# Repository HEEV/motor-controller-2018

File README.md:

# Cedarville University: Modular Motor Controller Project
### Senior Design project by Samuel Ellicott and Isaac Jones 2018-2019

You are in the hardware portion of the project, this contains the Kicad 
design files for the project and the schematics in PDF form. If you are 
looking for the software it is in the 
[motor controller 2018 sw](https://github.com/HEEV/motor-controller-2018-sw)
github repository. 

This project’s goal is to provide the Cedarville University Supermileage team with a high-efficiency electric motor controller for use in any category of vehicle. The controller should be simple enough to use that a competent freshman or sophomore engineer on the team could set it up. 

The controller is operated either by an analog throttle input or by the
CAN interface exposed by the controller. Hopefully this makes the controler
simple to use, but still capable of clever efficiency optimizations with
some wizardry.

The Cedarville supermileage team competes in the 
[Shell Eco-Marathon](https://www.shell.com/make-the-future/shell-ecomarathon.html)
so the design must fit within the contstraints of their rules (at the time of
this writting, 2019). This leads to the following constraints

* Maximum Nonminal Battery Voltage - 48V
* Peak Voltage - 60V

Therefore the controller was designed to fit these requirements and a new
driver stage would need to be designed if these limits were exceeded.

```
Even though I have graduated I am still more than willing to answer questions about this project :-) 

-Sam Ellicott
```

## Project Organization
Overall, the project is organized into two gitub repositories. 
This one, devoted to the motor controller hardware
([motor controller 2018](https://github.com/HEEV/motor-controller-2018))
and the other one ([motor controller 2018 sw](https://github.com/HEEV/motor-controller-2018-sw)) devoted to the motor controller
software.

The actual hardware of the project is split into three PCBs 
(and three corresponding Kcad projects)

The hardware repository is split between three [Kicad](http://kicad-pcb.org/)
projects.

* [motor-controller-hw](motor-controller-hw/): 
  This somewhat poorly named project contains the 
  files for the controller portion of the project (micocontroller, 
  FOC algorithm chip, inputs, etc)
* [MotorControllerPowerBoardRev2](MotorControllerPowerBoardRev2/MotorControllerPowerBoard):
  This contains (somewhat obviously) the Kicad project for the 
  power conversion part of the motor controller (FET driver chips, giant
  honking power MOSFETS, current sensing chips, etc). The power stage has 
  four NFET half bridges and three hall-effect current sensing chips.
  The board can be configured to power a 3-phase motor or a brushed motor.
  Optionally for the brushed motor the half-bridges can be parralled to 
  double the drive current capability. 
* [voltage-regulator-module](voltage-regulator-module/): 
  We were unable to find a commertially available 60V-to-5v DC-DC converter 
  for the controller portion of the project that did not have significant
  lead time, so we rolled our own to fit a similar footprint to some
  DC-DC converters from Pololu. This is just a little daughter PCB that
  is soldered to the controller PCB.  

The schematic files and PDF's of the PCB layout can be found in the 
[pdf](pdf) directory.

## Software versions
For this project we used either Kicad version 5.0.1 or 5.0.2 
(I cannot really remember), but it will probably work with any version
of Kicad > 5.0.0

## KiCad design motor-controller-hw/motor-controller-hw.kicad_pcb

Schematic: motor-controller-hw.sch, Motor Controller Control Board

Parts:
C101, C104, C105: 4u7; C_0805_HandSoldering; Digi-key# 732-7628-1-ND
C102: 100n; C_0805_HandSoldering; Digi-key# 1276-2444-1-ND
C103: 33u; CP_Radial_D8.0mm_P3.50mm; Digi-key# P10340-ND
D101: 15V Zener; D_SOD-123F; Digi-key# BZT52HC15WF-7DICT-ND‎
D102: D_USB; D_SOD-123F; Digi-key# MBR1020VLCT-ND‎
D103: Vin; LED_0603_HandSoldering; Digi-key# 732-12015-1-ND
D104: 5V; LED_0603_HandSoldering; Digi-key# 732-12015-1-ND
D105: 3.3V; LED_0603_HandSoldering; Digi-key# 732-12015-1-ND
F101, F102, F103, F105: 50mA PTC; Fuse_0603_1608Metric_Pad1.05x0.95mm_HandSolder; Digi-key# 507-1816-1-ND
F104: 120mA PTC; Fuse_0603_1608Metric_Pad1.05x0.95mm_HandSolder; Digi-key# 507-1819-1-ND
J101: CAN; Molex-duraClick-4conn; Digi-key# WM7171CT-ND
J102: Throttle; Molex-duraClick-4conn; Digi-key# WM7171CT-ND
J103: Motor T; Molex-duraClick-2conn; Digi-key# WM7169CT-ND
J104: Tran T; Molex-duraClick-2conn; Digi-key# WM7169CT-ND
J105: USB_B_Micro; USB_Micro-B; Digi-key# 609-4618-1-ND
J106: Extra IO; Molex-UltraFit-14p-vert; Digi-key# WM11743-ND‎
J107: Hall Sensors; MICRO_JST_6; Digi-key# 455-1708-ND
J108: CAN_DBG; PinHeader_1x02_P2.54mm_Vertical; Digi-key# S1212EC-02-ND
J109: ABN Encoder; PinHeader_1x05_P2.54mm_Vertical; Digi-key# S1212EC-05-ND
J110: SPI_DBG; PinHeader_1x04_P2.54mm_Vertical; Digi-key# S1212EC-04-ND
J111: Trinamic-Bridge; PinSocket_2x22_P2.54mm_Vertical; Digi-key# S7125-ND
JP101: 5v JP; PinHeader_1x02_P2.54mm_Vertical; Digi-key# S1212EC-02-ND
Q101: Q_PMOS_GDS; TO-252-3_TabPin2; Digi-key# 785-1102-1-ND
R101, R102, R103: 10K; R_0805_HandSoldering; Digi-key# A129761CT-ND
R104: 1K; R_0805_HandSoldering; Digi-key# A129749CT-ND
R105: 330R; R_0805_HandSoldering; Digi-key# 311-330CRCT-ND
TP101: Batt_TP; PinHeader_1x02_P2.54mm_Vertical; Digi-key# N/A
TP102: 5v_TP; PinHeader_1x02_P2.54mm_Vertical; Digi-key# N/A
TP103: 3v3_TP; PinHeader_1x02_P2.54mm_Vertical; Digi-key# N/A
TP104, TP105: GND_TP; PinHeader_1x01_P2.54mm_Vertical; Digi-key# N/A
U101: AP7361C-33; SOT-223; Digi-key# AP7361C-33E-13DICT-ND
U102: D36V6F5; D36V6Fx

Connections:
+3V3: C104.1, C105.1, F103.2, R101.1, R105.2, TP103.2, U101.3; also elsewhere on the board
+5V: C101.1, C102.1, D102.1, F101.1, F102.2, F104.1, F105.2, J109.5, J111.42, R104.2, TP102.2, U101.1, U102.1; also elsewhere on the board
+BATT: C103.1, D101.1, Q101.3, R103.2, TP101.2, U102.3; also elsewhere on the board
/ADC_I_A: J111.15; also elsewhere on the board
/ADC_I_B: J111.14; also elsewhere on the board
/A_Out1: J106.10; also elsewhere on the board
/A_Out2: J106.11; also elsewhere on the board
/A_in1: J106.3; also elsewhere on the board
/A_in2: J106.4; also elsewhere on the board
/Batt_Current: J111.16; also elsewhere on the board
/Brake: J111.36; also elsewhere on the board
/CAN_H: J101.3; also elsewhere on the board
/CAN_L: J101.2; also elsewhere on the board
/D_Out1: J106.12; also elsewhere on the board
/D_Out2: J106.13; also elsewhere on the board
/D_in1: J106.5; also elsewhere on the board
/D_in2: J106.6; also elsewhere on the board
/D_in3: J106.7; also elsewhere on the board
/D_in4: J106.14; also elsewhere on the board
/ENC_A_in: J109.4; also elsewhere on the board
/ENC_B_in: J109.3; also elsewhere on the board
/ENC_N_in: J109.2; also elsewhere on the board
/En_Out: J111.40; also elsewhere on the board
/HallA_in: J107.3; also elsewhere on the board
/HallB_in: J107.4; also elsewhere on the board
/HallC_in: J107.5; also elsewhere on the board
/IO Protection/CAN_Rx: J108.1; also elsewhere on the board
/IO Protection/CAN_Tx: J108.2; also elsewhere on the board
/MotorTemp: J103.2, J107.2, R101.2; also elsewhere on the board
/PWM_AH: J111.18; also elsewhere on the board
/PWM_AL: J111.17; also elsewhere on the board
/PWM_BH: J111.20; also elsewhere on the board
/PWM_BL: J111.19; also elsewhere on the board
/PWM_CH: J111.22; also elsewhere on the board
/PWM_CL: J111.21; also elsewhere on the board
/PWM_DH: J111.26; also elsewhere on the board
/PWM_DL: J111.23; also elsewhere on the board
/PWM_Idle_H: J111.34; also elsewhere on the board
/PWM_Idle_L: J111.35; also elsewhere on the board
/SPI_MISO: J111.28; also elsewhere on the board
/SPI_MOSI: J111.32; also elsewhere on the board
/SPI_SCK: J111.27; also elsewhere on the board
/SPI_SS: J111.24; also elsewhere on the board
/TMC4671/SPI_MISO: J110.3; also elsewhere on the board
/TMC4671/SPI_MOSI: J110.4; also elsewhere on the board
/TMC4671/SPI_SCK: J110.2; also elsewhere on the board
/TMC4671/~SPI_CS: J110.1; also elsewhere on the board
/Throttle: J102.2; also elsewhere on the board
/TransistorTemp: J104.2; also elsewhere on the board
/USB_D+: J105.3; also elsewhere on the board
/USB_D-: J105.2; also elsewhere on the board
/V_USB: D102.2, J105.1
/Vin: J111.1, Q101.2
GNDD: C101.2, C102.2, C103.2, C104.2, C105.2, D103.1, D104.1, D105.1, J101.1, J102.1, J103.1, J104.1, J105.5, J105.6, J106.1, J106.2, J107.6, J109.1, J111.2, J111.3, J111.43, J111.44, R102.2, TP101.1, TP102.1, TP103.1, TP104.1, TP105.1, U101.2, U102.2; also elsewhere on the board
unnamed: D101.2, Q101.1, R102.1
unnamed: D103.2, R103.1
unnamed: D104.2, R104.1
unnamed: D105.2, R105.1
unnamed: F101.2, J102.3, J102.4
unnamed: F102.1, J106.8
unnamed: F103.1, J106.9
unnamed: F104.2, JP101.2
unnamed: F105.1, J107.1
unnamed: J101.4, JP101.1

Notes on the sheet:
3.3V linear voltage regulator for the low voltage electronics. The selected regulator can supply 1A of output current, which is more than what the 5V switching regulator can supply. The 4.7uF output capacitor should have a fairly low ESR.
5V switching regulator, up to 50V input, maximum 600mA output current. The regulator is short circuit protected. A P-Channel MOSFET is used as an ideal diode with a 18v zener diode to protect the MOSFET gate. The 10K resistor limits the zener diode current to 3mA at 48V input. A Schotty diode is us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
Power supply test points
PWM_Ax, PWM_Bx, and PWM_Cx correspond to the A, B, and C phases of a three phase motor. The PWM_Dx lines are for a "extra" fourth phase. Note that the A, B, and C lines may be labeled U, V, and W elsewhere which are their european designation.
Digital Comm
Analog IO
Encoders
Power Status LEDs

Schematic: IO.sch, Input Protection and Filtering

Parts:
C201, C204, C205, C206, C207, C208, C209, C210, C211: 100n; C_0805_HandSoldering; Digi-key# 1276-2444-1-ND
C202, C212, C213: 1u; C_0805_HandSoldering; Digi-key# 732-7672-1-ND
C203: 150n; C_0805_HandSoldering; Digi-key# 732-7674-1-ND
C214: 4u7; C_0805_HandSoldering; Digi-key# 732-7628-1-ND
C215, C216, C217, C218, C219, C220: 100p; C_0805_HandSoldering; Digi-key# 1276-1014-1-ND
JP201: CAN Term; PinHeader_1x02_P2.54mm_Vertical
R201, R202, R203, R204, R205: 2K; R_0805_HandSoldering
R206: 3K9; R_0805_HandSoldering
R207, R208, R209, R213, R214, R215: 100R; R_0805_HandSoldering
R210, R211, R212, R217, R218, R219: 4K7; R_0805_HandSoldering
R216: 120R; R_0805_HandSoldering
R220: 10K; R_0805_HandSoldering
U201, U202, U203: MCP6004; SOIC-14_3.9x8.7mm_P1.27mm; Digi-key# MCP6004-I/SL-ND‎
U204, U205: 74HC7014; SOIC-14_3.9x8.7mm_P1.27mm; Digi-key# 1727-6342-1-ND
U206: mcp2562; SOIC-8_3.9x4.9mm_P1.27mm; Digi-key# 568-11881-1-ND

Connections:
+3V3: C208.1, C209.1, C210.1, C211.1, C212.1, C213.1, C214.1, U202.4, U203.4, U204.14, U205.14, U206.5; also elsewhere on the board
+5V: C201.1, C202.1, R210.1, R211.1, R212.1, R217.1, R218.1, R219.1, U201.4, U206.3; also elsewhere on the board
/A_Out1: U201.6, U201.7; also elsewhere on the board
/A_Out2: U201.1, U201.2; also elsewhere on the board
/A_in1: U203.3; also elsewhere on the board
/A_in2: U203.10; also elsewhere on the board
/CAN_H: R216.1, U206.7; also elsewhere on the board
/CAN_L: JP201.1, U206.6; also elsewhere on the board
/D_Out1: U204.10; also elsewhere on the board
/D_Out2: U204.12; also elsewhere on the board
/D_in1: U204.1; also elsewhere on the board
/D_in2: U204.3; also elsewhere on the board
/D_in3: U204.5; also elsewhere on the board
/D_in4: U204.9; also elsewhere on the board
/ENC_A: U205.8; also elsewhere on the board
/ENC_A_in: R213.2; also elsewhere on the board
/ENC_B: U205.10; also elsewhere on the board
/ENC_B_in: R214.2; also elsewhere on the board
/ENC_N: U205.12; also elsewhere on the board
/ENC_N_in: R215.2; also elsewhere on the board
/HallA: U205.2; also elsewhere on the board
/HallA_in: R207.2; also elsewhere on the board
/HallB: U205.4; also elsewhere on the board
/HallB_in: R208.2; also elsewhere on the board
/HallC: U205.6; also elsewhere on the board
/HallC_in: R209.2; also elsewhere on the board
/IO Protection/A_In1: U203.6, U203.7; also elsewhere on the board
/IO Protection/A_In2: U203.13, U203.14; also elsewhere on the board
/IO Protection/A_Out1: U201.5; also elsewhere on the board
/IO Protection/A_Out2: U201.3; also elsewhere on the board
/IO Protection/CAN_Rx: U206.4; also elsewhere on the board
/IO Protection/CAN_Tx: U206.1; also elsewhere on the board
/IO Protection/D_In1: U204.2; also elsewhere on the board
/IO Protection/D_In2: U204.4; also elsewhere on the board
/IO Protection/D_In3: U204.6; also elsewhere on the board
/IO Protection/D_In4: U204.8; also elsewhere on the board
/IO Protection/D_Out1: U204.11; also elsewhere on the board
/IO Protection/D_Out2: U204.13; also elsewhere on the board
/IO Protection/MotorTemp: U202.6, U202.7; also elsewhere on the board
/IO Protection/Throttle: U201.13, U201.14; also elsewhere on the board
/IO Protection/TransistorTemp: U202.13, U202.14; also elsewhere on the board
/MotorTemp: U202.3; also elsewhere on the board
/Throttle: U201.10; also elsewhere on the board
/TransistorTemp: U202.10; also elsewhere on the board
GNDD: C201.2, C202.2, C203.2, C204.2, C205.2, C206.2, C207.2, C208.2, C209.2, C210.2, C211.2, C212.2, C213.2, C214.2, C215.2, C216.2, C217.2, C218.2, C219.2, C220.2, R206.1, R220.1, U201.11, U202.11, U203.11, U204.7, U205.7, U206.2; also elsewhere on the board
unnamed: C203.1, R201.1, R206.2, U201.12
unnamed: C204.1, R202.1, U202.5
unnamed: C205.1, R203.1, U202.12
unnamed: C206.1, R204.1, U203.5
unnamed: C207.1, R205.1, U203.12
unnamed: C215.1, R207.1, R210.2, U205.1
unnamed: C216.1, R208.1, R211.2, U205.3
unnamed: C217.1, R209.1, R212.2, U205.5
unnamed: C218.1, R213.1, R217.2, U205.9
unnamed: C219.1, R214.1, R218.2, U205.11
unnamed: C220.1, R215.1, R219.2, U205.13
unnamed: JP201.2, R216.2
unnamed: R201.2, U201.8, U201.9
unnamed: R202.2, U202.1, U202.2
unnamed: R203.2, U202.8, U202.9
unnamed: R204.2, U203.1, U203.2
unnamed: R205.2, U203.8, U203.9
unnamed: R220.2, U206.8

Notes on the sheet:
Rail to rail op-amp necessary for the filter section to work correctly. Throttle and output buffers run off 5v supply, all others on 3.3v to prevent ADC damage.
Buffer input stage
Attenuator and Filter Selected for 750Hz cutoff 1.5Khz Sampling rate
Buffer output stage
Output Buffers
Input Buffers
Hall Input Filtering
Power and Bypass Capacitors
MCP2562 may be replaced with a TJF1051T/3. Pin 5 on the TJF1051T/3 is a silent mode enable pin which is active high, so the circuit still works.
CAN Tranciever PHY
This sheet contains input/output proteciton and conditioning circuitry. Note that the stm32 USB lines pass through this sheet without modification.
ABN Encoder Input Filtering
Schmitt trigger inputs for taking out noise

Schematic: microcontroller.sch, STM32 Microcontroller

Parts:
C301, C302, C303, C304, C305, C311: 100n; C_0805_HandSoldering; Digi-key# 1276-2444-1-ND
C306: 4u7; C_0805_HandSoldering; Digi-key# 732-7628-1-ND
C307: 1u; C_0805_HandSoldering; Digi-key# 732-7672-1-ND
C308: 10n; C_0805_HandSoldering; Digi-key# 732-12169-1-ND
C309, C310: 27pf; C_0805_HandSoldering; Digi-key# 1276-2622-1-ND
D301: CAN_Status; LED_0603_1608Metric_Pad1.05x0.95mm_HandSolder; Digi-key# 732-12013-1-ND
D302: Heartbeat; LED_0603_1608Metric_Pad1.05x0.95mm_HandSolder; Digi-key# 732-12015-1-ND
D303: User_LED; LED_0603_1608Metric_Pad1.05x0.95mm_HandSolder; Digi-key# 732-12017-1-ND
J301: SWD; PinHeader_1x06_P2.54mm_Vertical; Digi-key# S1212EC-06-ND
J302: User USART; PinHeader_1x03_P2.54mm_Vertical; Digi-key# S1212EC-03-ND
R301: 10K; R_0805_HandSoldering; Digi-key# A129761CT-ND
R302, R306, R307: 330R; R_0805_HandSoldering; Digi-key# 311-330CRCT-ND
R303: 4K7; R_0805_HandSoldering; Digi-key# 311-4.70KCRCT-ND
R304, R305: 100R; R_0805_HandSoldering; Digi-key# 311-100CRCT-ND
R308: 1K5; R_0805_2012Metric
SW301: Reset; SW_SPST_FSMSM; Digi-key# 450-1758-1-ND
SW302: Boot; SW_SPST_FSMSM; Digi-key# 450-1758-1-ND
SW303: User_SW; SW_SPST_FSMSM; Digi-key# 450-1758-1-ND
U301: STM32F303RETx; LQFP-64_10x10mm_P0.5mm; Digi-key# 497-15163-ND
Y301: 8Mhz; Crystal_SMD_HC49-SD_HandSoldering; Digi-key# 535-10212-1-ND‎

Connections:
+3V3: C301.1, C302.1, C304.1, C305.1, C306.1, C307.1, C308.1, J301.1, R303.1, R308.1, SW302.2, U301.1 (VBAT), U301.13 (VDDA), U301.19 (VDD), U301.32 (VDD), U301.48 (VDD), U301.64 (VDD); also elsewhere on the board
/IO Protection/A_In1: U301.23 (PA7); also elsewhere on the board
/IO Protection/A_In2: U301.24 (PC4); also elsewhere on the board
/IO Protection/A_Out1: U301.20 (PA4); also elsewhere on the board
/IO Protection/A_Out2: U301.21 (PA5); also elsewhere on the board
/IO Protection/CAN_Rx: U301.61 (PB8); also elsewhere on the board
/IO Protection/CAN_Tx: U301.62 (PB9); also elsewhere on the board
/IO Protection/D_In1: U301.37 (PC6); also elsewhere on the board
/IO Protection/D_In2: U301.38 (PC7); also elsewhere on the board
/IO Protection/D_In3: U301.39 (PC8); also elsewhere on the board
/IO Protection/D_In4: U301.40 (PC9); also elsewhere on the board
/IO Protection/D_Out1: U301.41 (PA8); also elsewhere on the board
/IO Protection/D_Out2: U301.42 (PA9); also elsewhere on the board
/IO Protection/MotorTemp: U301.14 (PA0); also elsewhere on the board
/IO Protection/Throttle: U301.22 (PA6); also elsewhere on the board
/IO Protection/TransistorTemp: U301.15 (PA1); also elsewhere on the board
/SPI_MISO: U301.53 (PC12); also elsewhere on the board
/SPI_MOSI: U301.52 (PC11); also elsewhere on the board
/SPI_SCK: U301.51 (PC10); also elsewhere on the board
/SPI_SS: U301.50 (PA15); also elsewhere on the board
/STM32/Boot: R301.1, SW302.1, U301.60 (BOOT0)
/STM32/CAN_Status: R305.2, U301.26 (PB0)
/STM32/Heartbeat: R306.2, U301.27 (PB1)
/STM32/JTCK: J301.2, U301.49 (PA14)
/STM32/JTMS: J301.4, U301.46 (PA13)
/STM32/OSC+: C309.1, U301.5 (PF0), Y301.2
/STM32/OSC-: R302.1, U301.6 (PF1)
/STM32/Reset: C303.1, J301.5, SW301.2, U301.7 (NRST)
/STM32/SWO: J301.6, U301.55 (PB3)
/STM32/USART_Rx: J302.3, U301.17 (PA3)
/STM32/USART_Tx: J302.2, U301.16 (PA2)
/STM32/User_LED: R307.2, U301.28 (PB2)
/STM32/User_SW: C311.1, R303.2, SW303.2, U301.2 (PC13)
/TMC4671/En_In: U301.29 (PB10); also elsewhere on the board
/TMC4671/SPI_MISO: U301.35 (PB14); also elsewhere on the board
/TMC4671/SPI_MOSI: U301.36 (PB15); also elsewhere on the board
/TMC4671/SPI_SCK: U301.34 (PB13); also elsewhere on the board
/TMC4671/Status: U301.30 (PB11); also elsewhere on the board
/TMC4671/~SPI_CS: U301.33 (PB12); also elsewhere on the board
/USB_D+: R308.2, U301.45 (PA12); also elsewhere on the board
/USB_D-: U301.44 (PA11); also elsewhere on the board
GNDD: C301.2, C302.2, C303.2, C304.2, C305.2, C306.2, C307.2, C308.2, C309.2, C310.2, D301.1, D302.1, D303.1, J301.3, J302.1, R301.2, R304.2, SW301.1, SW303.1, U301.12 (VSSA), U301.18 (VSS), U301.31 (VSS), U301.47 (VSS), U301.63 (VSS); also elsewhere on the board
unnamed: C310.1, R302.2, Y301.1
unnamed: C311.2, R304.1
unnamed: D301.2, R305.1
unnamed: D302.2, R306.1
unnamed: D303.2, R307.1

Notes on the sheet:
Bypass Capacitors, one for each Vdd pin, and a 4.7uf cap for good measure. Also two bypass capacitors (1uf and 10nf) for the ADC and DAC.
Crystal Oscilator with 18pf load capacitor rating. Assumed stray capacitance of 5pf. See: https://www.allaboutcircuits.com/technical-articles/ choosing-the-right-oscillator-for-your-microcontroller/
Reset and Boot switches for programming the microcontroller with the USB bootloader. SWD connector for in system debugging of the microcontroller.
User Inputs and Outputs
1.5 KOhm pull up: enable USB programming

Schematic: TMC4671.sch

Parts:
C401, C402, C403, C404, C405, C406, C407, C408, C409, C412, C413, C414, C415: 100n; C_0805_HandSoldering; Digi-key# 1276-2444-1-ND
C410: 470n; C_0805_HandSoldering; Digi-key# 732-7670-1-ND
C411, C416: 4u7; C_0805_HandSoldering; Digi-key# 732-7628-1-ND
C417, C418, C419, C420: 10n; C_0805_HandSoldering; Digi-key# 732-12169-1-ND
J401: Trinamic_TRMI; DF20F-10DP-1V(56); Digi-key# H10726CT-ND
J402: TMC4671 USART; PinHeader_1x03_P2.54mm_Vertical; Digi-key# S1212EC-03-ND
R401, R402, R403, R404, R405, R408, R409: 10K; R_0805_HandSoldering; Digi-key# A129761CT-ND
R406, R407: 100R; R_0805_HandSoldering; Digi-key# 311-100CRCT-ND
R410: 110K; R_0805_HandSoldering; Digi-key# 311-110KCRCT-ND
TP401: B_Ref; Pin_Header_Straight_1x01_Pitch2.54mm; Digi-key# N/A
TP402: A_Ref; Pin_Header_Straight_1x01_Pitch2.54mm; Digi-key# N/A
TP403, TP404, TP405, TP406, TP407, TP408, TP409, TP410, TP411, TP412, TP413, TP414, TP415, TP416, TP417, TP418: TestPoint; TestPoint_Pad_D1.0mm; Digi-key# N/A
TP419: A_I_TP; PinHeader_1x02_P2.54mm_Vertical; Digi-key# N/A
TP420: B_I_TP; PinHeader_1x02_P2.54mm_Vertical; Digi-key# N/A
TP421: Batt_V_TP; PinHeader_1x02_P2.54mm_Vertical; Digi-key# N/A
TP422: Batt_I_TP; PinHeader_1x02_P2.54mm_Vertical; Digi-key# N/A
U401: TMC4671; QFN76P; Digi-key# 1460-1302-ND
X401: IQXO-50; Clock-FOX924; Digi-key# ‎631-1074-1-ND‎

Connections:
+3V3: C401.1, C403.1, C404.1, C405.1, C406.1, C408.1, C409.1, C410.1, C411.1, J401.1, R405.1, U401.2, U401.13, U401.43, U401.52, U401.61, U401.72, X401.4; also elsewhere on the board
+5V: C415.1, C416.1, R401.1, R403.1, U401.23; also elsewhere on the board
+BATT: R410.1; also elsewhere on the board
/ADC_I_A: R406.1; also elsewhere on the board
/ADC_I_B: R407.1; also elsewhere on the board
/Batt_Current: R409.1; also elsewhere on the board
/Brake: U401.31; also elsewhere on the board
/ENC_A: U401.35; also elsewhere on the board
/ENC_B: U401.34; also elsewhere on the board
/ENC_N: U401.33; also elsewhere on the board
/En_Out: U401.32; also elsewhere on the board
/HallA: U401.38; also elsewhere on the board
/HallB: U401.37; also elsewhere on the board
/HallC: U401.36; also elsewhere on the board
/PWM_AH: U401.39; also elsewhere on the board
/PWM_AL: U401.40; also elsewhere on the board
/PWM_BH: U401.41; also elsewhere on the board
/PWM_BL: U401.42; also elsewhere on the board
/PWM_CH: U401.46; also elsewhere on the board
/PWM_CL: U401.47; also elsewhere on the board
/PWM_DH: U401.48; also elsewhere on the board
/PWM_DL: U401.49; also elsewhere on the board
/PWM_Idle_H: U401.59; also elsewhere on the board
/PWM_Idle_L: U401.60; also elsewhere on the board
/TMC4671/1v8: C412.1, C413.1, C414.1, U401.15, U401.45, U401.63
/TMC4671/A_Current: C417.1, R406.2, TP419.2, U401.16
/TMC4671/A_Current_Ref: C402.1, R401.2, R402.1, TP401.1, U401.17
/TMC4671/B_Current: C418.1, R407.2, TP420.2, U401.18
/TMC4671/B_Current_Ref: C407.1, R403.2, R404.1, TP402.1, U401.19
/TMC4671/Batt_I: C420.1, R409.2, TP422.2, U401.21
/TMC4671/Batt_V: C419.1, R408.1, R410.2, TP421.2, U401.20
/TMC4671/CLK: U401.51, X401.3
/TMC4671/En_In: U401.55; also elsewhere on the board
/TMC4671/RTMI_CS: J401.3, U401.75
/TMC4671/RTMI_MISO: J401.9, U401.4
/TMC4671/RTMI_MOSI: J401.7, U401.1
/TMC4671/RTMI_SCK: J401.5, U401.76
/TMC4671/RTMI_TRG: J401.4, U401.5
/TMC4671/SPI_MISO: U401.9; also elsewhere on the board
/TMC4671/SPI_MOSI: U401.8; also elsewhere on the board
/TMC4671/SPI_SCK: U401.7; also elsewhere on the board
/TMC4671/Status: U401.12; also elsewhere on the board
/TMC4671/USART_Rx: J402.3, U401.10
/TMC4671/USART_Tx: J402.2, U401.11
/TMC4671/~SPI_CS: U401.6; also elsewhere on the board
GNDD: C401.2, C402.2, C403.2, C404.2, C405.2, C406.2, C407.2, C408.2, C409.2, C410.2, C411.2, C412.2, C413.2, C414.2, C415.2, C416.2, C417.2, C418.2, C419.2, C420.2, J401.6, J401.8, J401.10, J402.1, R402.2, R404.2, R408.2, TP419.1, TP420.1, TP421.1, TP422.1, U401.0, U401.3, U401.14, U401.24, U401.44, U401.53, U401.54, U401.62, U401.73, X401.2; also elsewhere on the board
unnamed: R405.2, U401.50
unnamed: TP403.1, U401.56
unnamed: TP404.1, U401.57
unnamed: TP405.1, U401.58
unnamed: TP406.1, U401.67
unnamed: TP407.1, U401.68
unnamed: TP408.1, U401.69
unnamed: TP409.1, U401.25
unnamed: TP410.1, U401.26
unnamed: TP411.1, U401.27
unnamed: TP412.1, U401.28
unnamed: TP413.1, U401.29
unnamed: TP414.1, U401.30
unnamed: TP415.1, U401.22
unnamed: TP416.1, U401.70
unnamed: TP417.1, U401.71
unnamed: TP418.1, U401.74

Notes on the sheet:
Phase current low pass filters RC constant set for 159KHz
Battery Voltage and Current Current RC filter set for 159KHz Voltage RC filter set for 1.59KHz
Voltage references for the current measurement ADC's
TMC4671 Debug interfaces
Decoupling capacitors
TMC4671 Clock Chip
SDE 4-30-19: TMC4671 hardware issue causes R408 to be changed from 10K to 3.3K. The same issue necessitates the addition of a 10K resistor "piggiebacked" on C420.

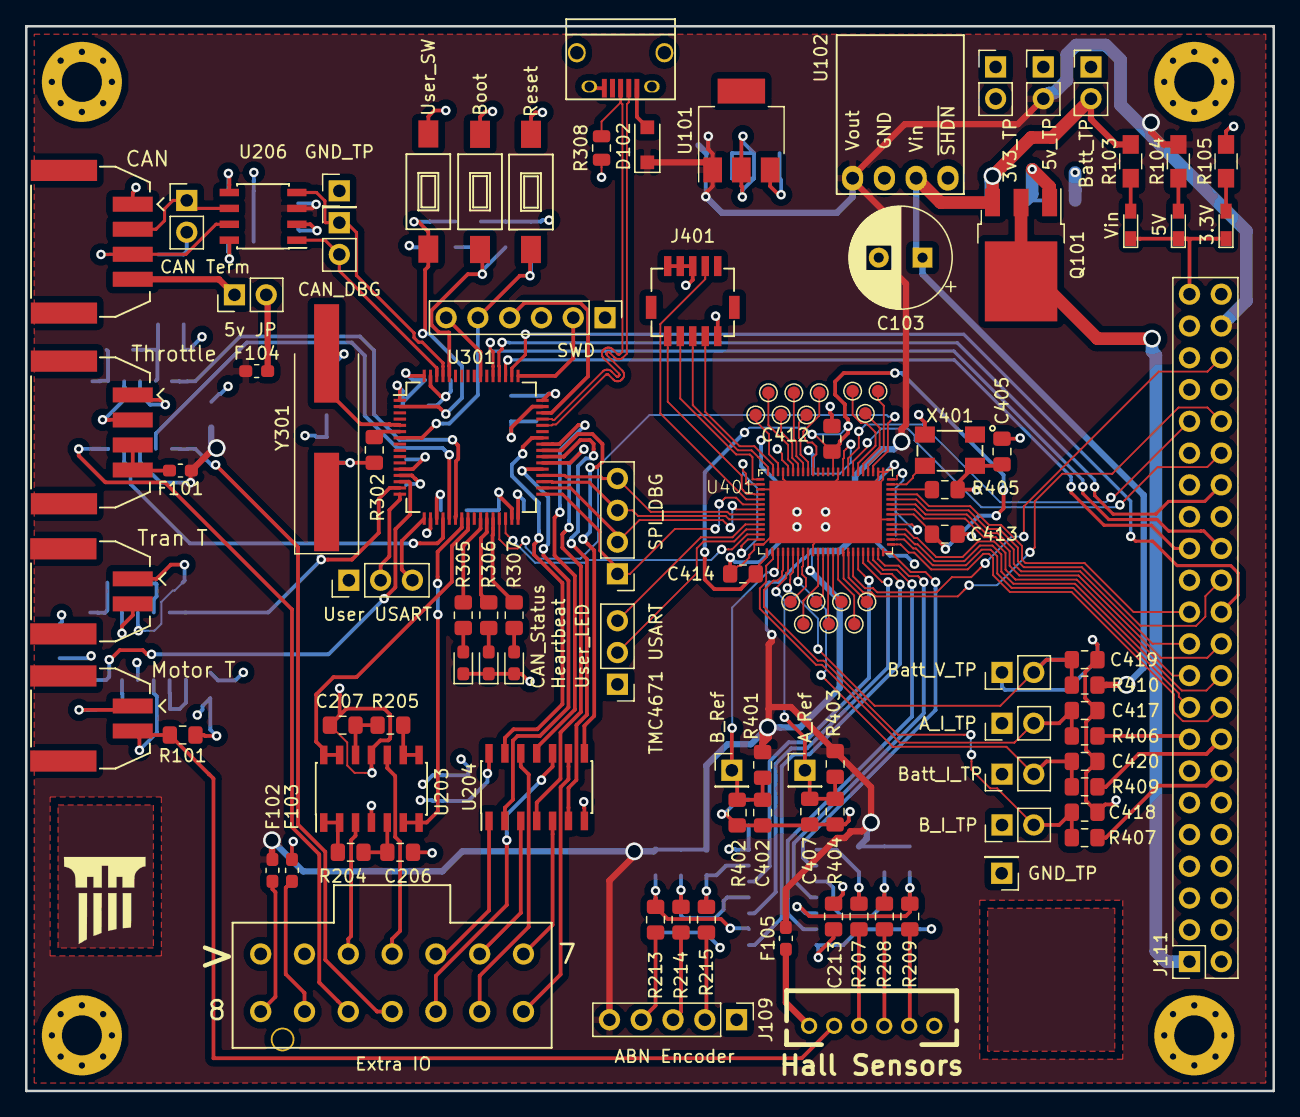
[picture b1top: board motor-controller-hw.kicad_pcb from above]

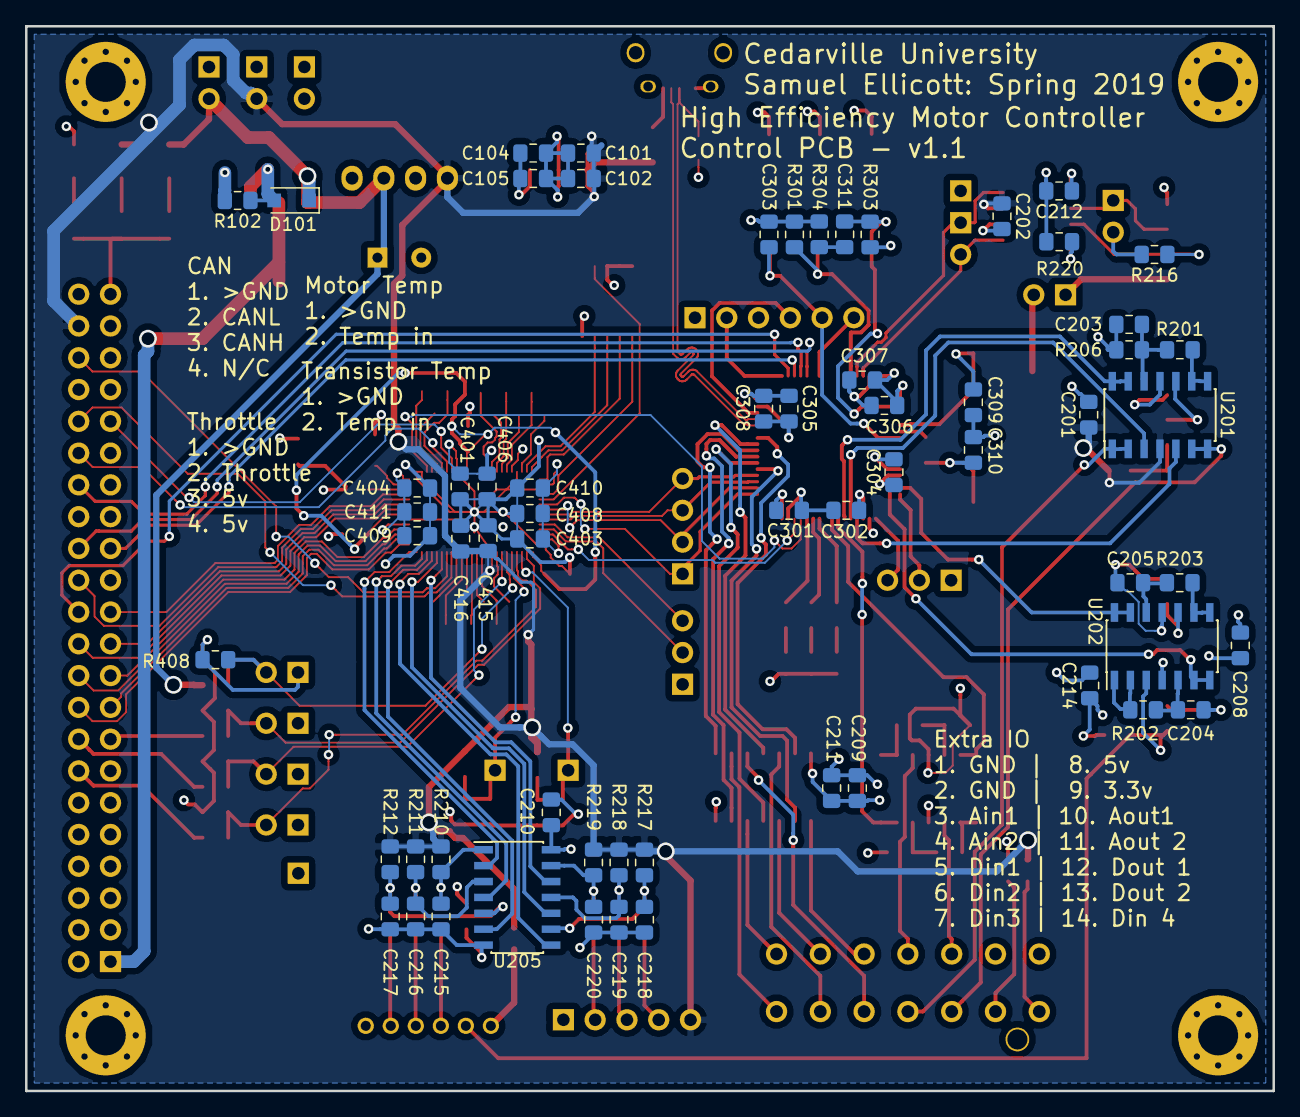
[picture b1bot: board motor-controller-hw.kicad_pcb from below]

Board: 4 copper layers, 99.7 x 85.1 mm, 172 parts (63 on the bottom side), 153 nets.
